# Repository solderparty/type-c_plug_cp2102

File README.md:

# CP2102 USB to Serial/UART with USB Type-C Plug

A simple breakout board for the CP2102 USB-to-Serial chip.

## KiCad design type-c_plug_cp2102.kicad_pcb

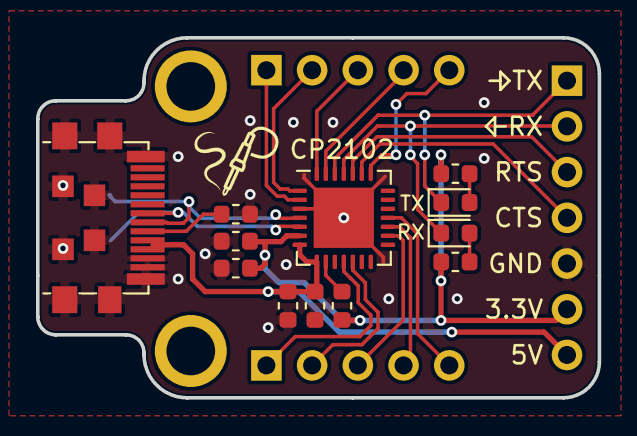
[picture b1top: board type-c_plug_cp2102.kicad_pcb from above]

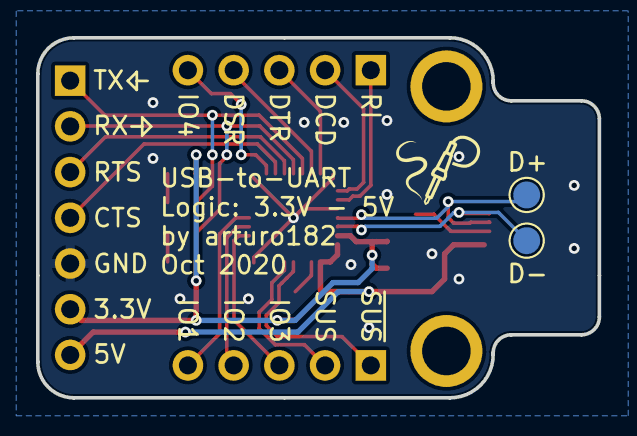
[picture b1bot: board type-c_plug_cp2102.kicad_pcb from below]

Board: 2 copper layers, 31.2 x 20.0 mm, 17 parts (2 on the bottom side), 23 nets.

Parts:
C1, C3: 0.1uF; C_0603_1608Metric
C2, C4: 4.7uF; C_0603_1608Metric
D1: LED_RXD; LED_0603_1608Metric
D2: LED_TXD; LED_0603_1608Metric
J1: USB_C_Plug_USB2.0; USB_C_Plug_UTC009-C12
J2: Conn_01x07; PinHeader_1x07_P2.54mm_Vertical
J3, J4: Conn_01x05; PinHeader_1x05_P2.54mm_Vertical
R1, R2: 1K; R_0603_1608Metric
R3: 5.1K; R_0603_1608Metric
R4: 10K; R_0603_1608Metric
TP1: TP_D-; TestPoint_Pad_D1.5mm
TP2: TP_D+; TestPoint_Pad_D1.5mm
U1: CP2102N-Axx-xQFN28; QFN-28-1EP_5x5mm_P0.5mm_EP3.35x3.35mm

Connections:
+3V3: C1.1, C2.1, J2.6, R1.2, R2.2, R4.2, U1.6 (VDD)
/D+: J1.A6 (D+), TP2.1, U1.4 (D+)
/D-: J1.A7 (D-), TP1.1, U1.5 (D-)
/GPIO1: J3.5, U1.18 (~RXT~/GPIO.1)
/GPIO2: J3.4, U1.17 (RS485/GPIO.2)
/GPIO3: J3.3, U1.16 (~WAKEUP~/GPIO.3)
/GPIO4: J4.5, U1.22 (GPIO.4)
/RXD: D1.1 (K), J2.2, U1.25 (RXD)
/SUSPEND: J3.2, U1.12 (SUSPEND)
/TXD: D2.1 (K), J2.1, U1.26 (TXD)
/~CTS~: J2.4, U1.23 (~CTS)
/~DCD~: J4.2, U1.1 (~DCD)
/~DSR~: J4.4, U1.27 (~DSR)
/~DTR~: J4.3, U1.28 (~DTR)
/~RI~: J4.1, U1.2 (~RI~/CLK)
/~RTS~: J2.3, U1.24 (~RTS)
/~SUSPEND~: J3.1, U1.11 (~SUSPEND)
GND: C1.2, C2.2, C3.2, C4.2, J1.A1 (GND), J1.B12 (GND), J1.S1 (SHIELD), J2.5, R3.1, U1.3 (GND), U1.29 (GND)
unnamed: D1.2 (A), R1.1
unnamed: D2.2 (A), R2.1
unnamed: J1.A5 (CC), R3.2
unnamed: R4.1, U1.9 (~RST)
VBUS: C3.1, C4.1, J1.A4 (VBUS), J1.B9 (VBUS), J2.7, U1.7 (VREGIN), U1.8 (VBUS)

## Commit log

2021-02-02 Initial import
